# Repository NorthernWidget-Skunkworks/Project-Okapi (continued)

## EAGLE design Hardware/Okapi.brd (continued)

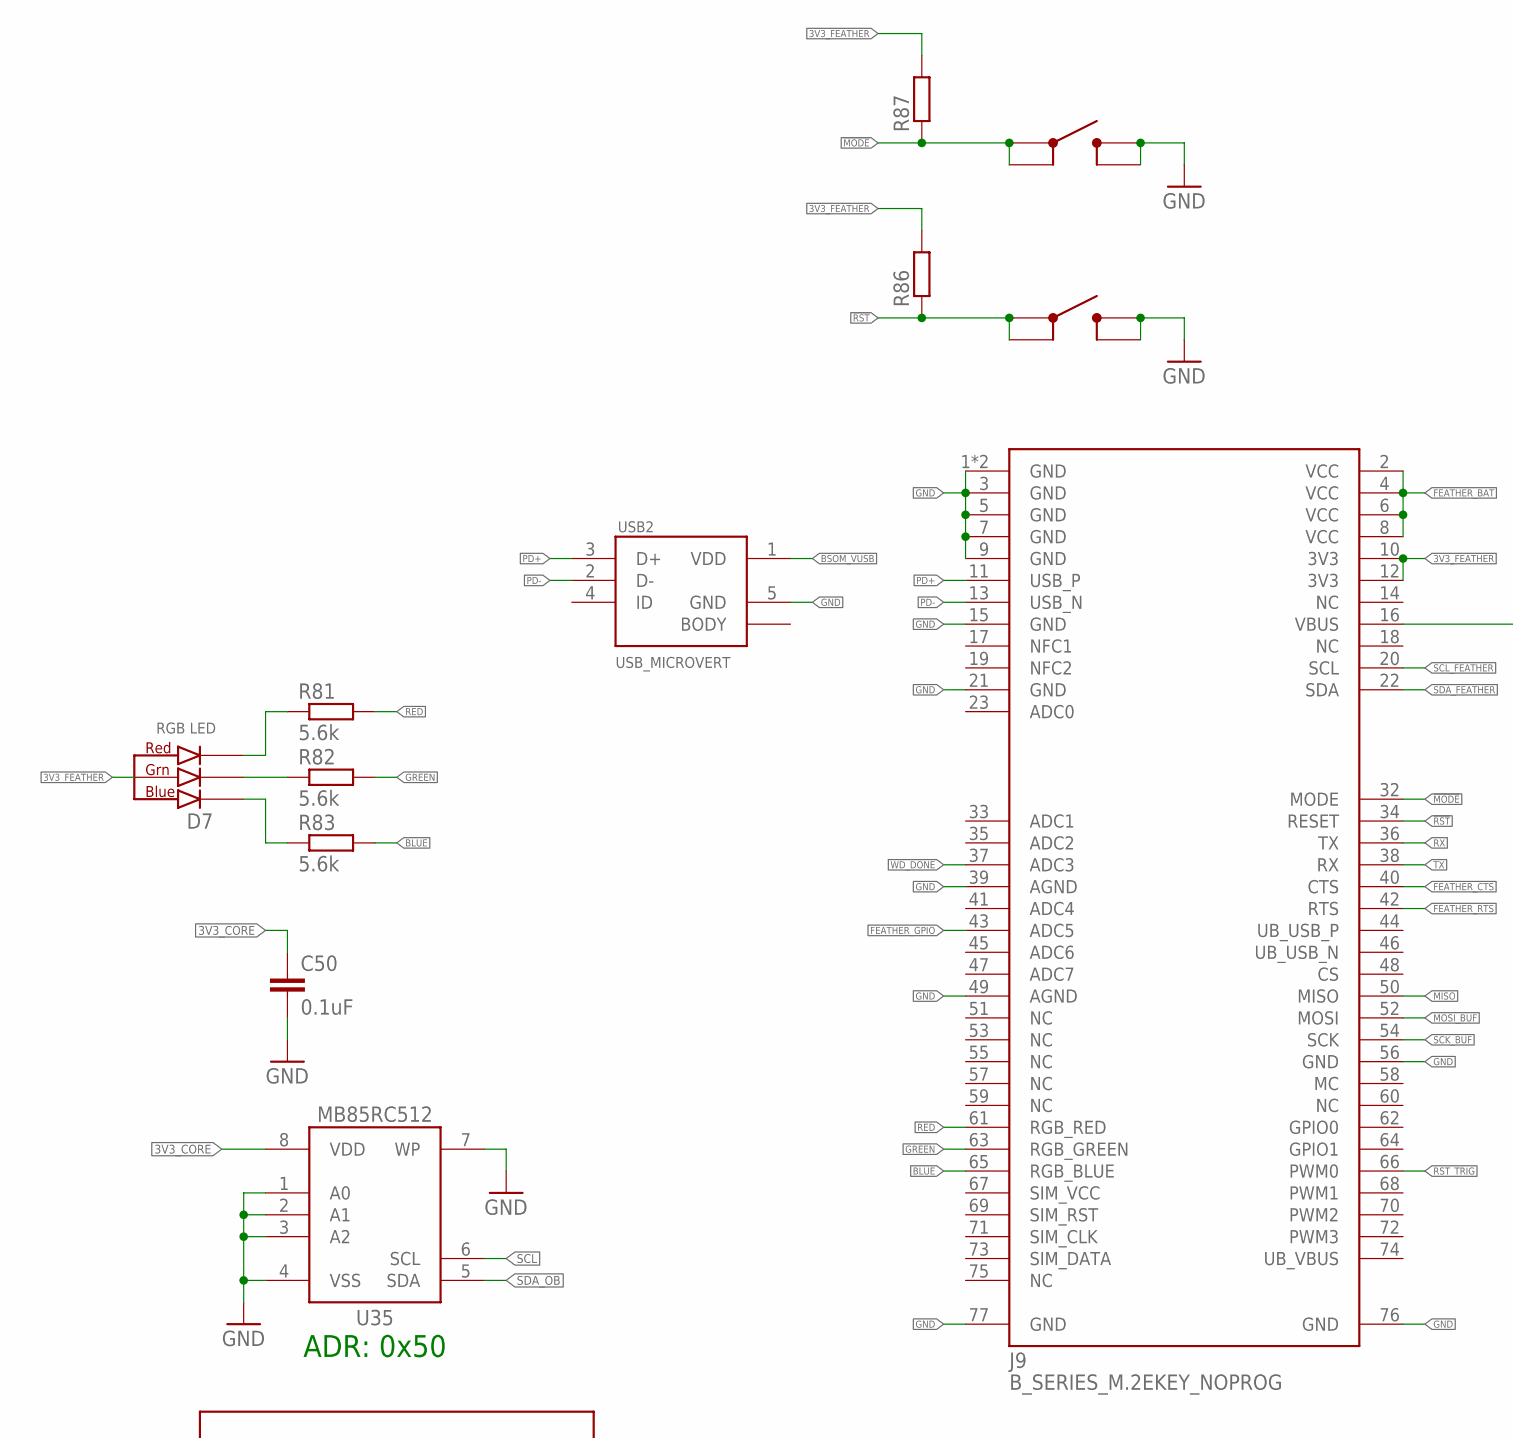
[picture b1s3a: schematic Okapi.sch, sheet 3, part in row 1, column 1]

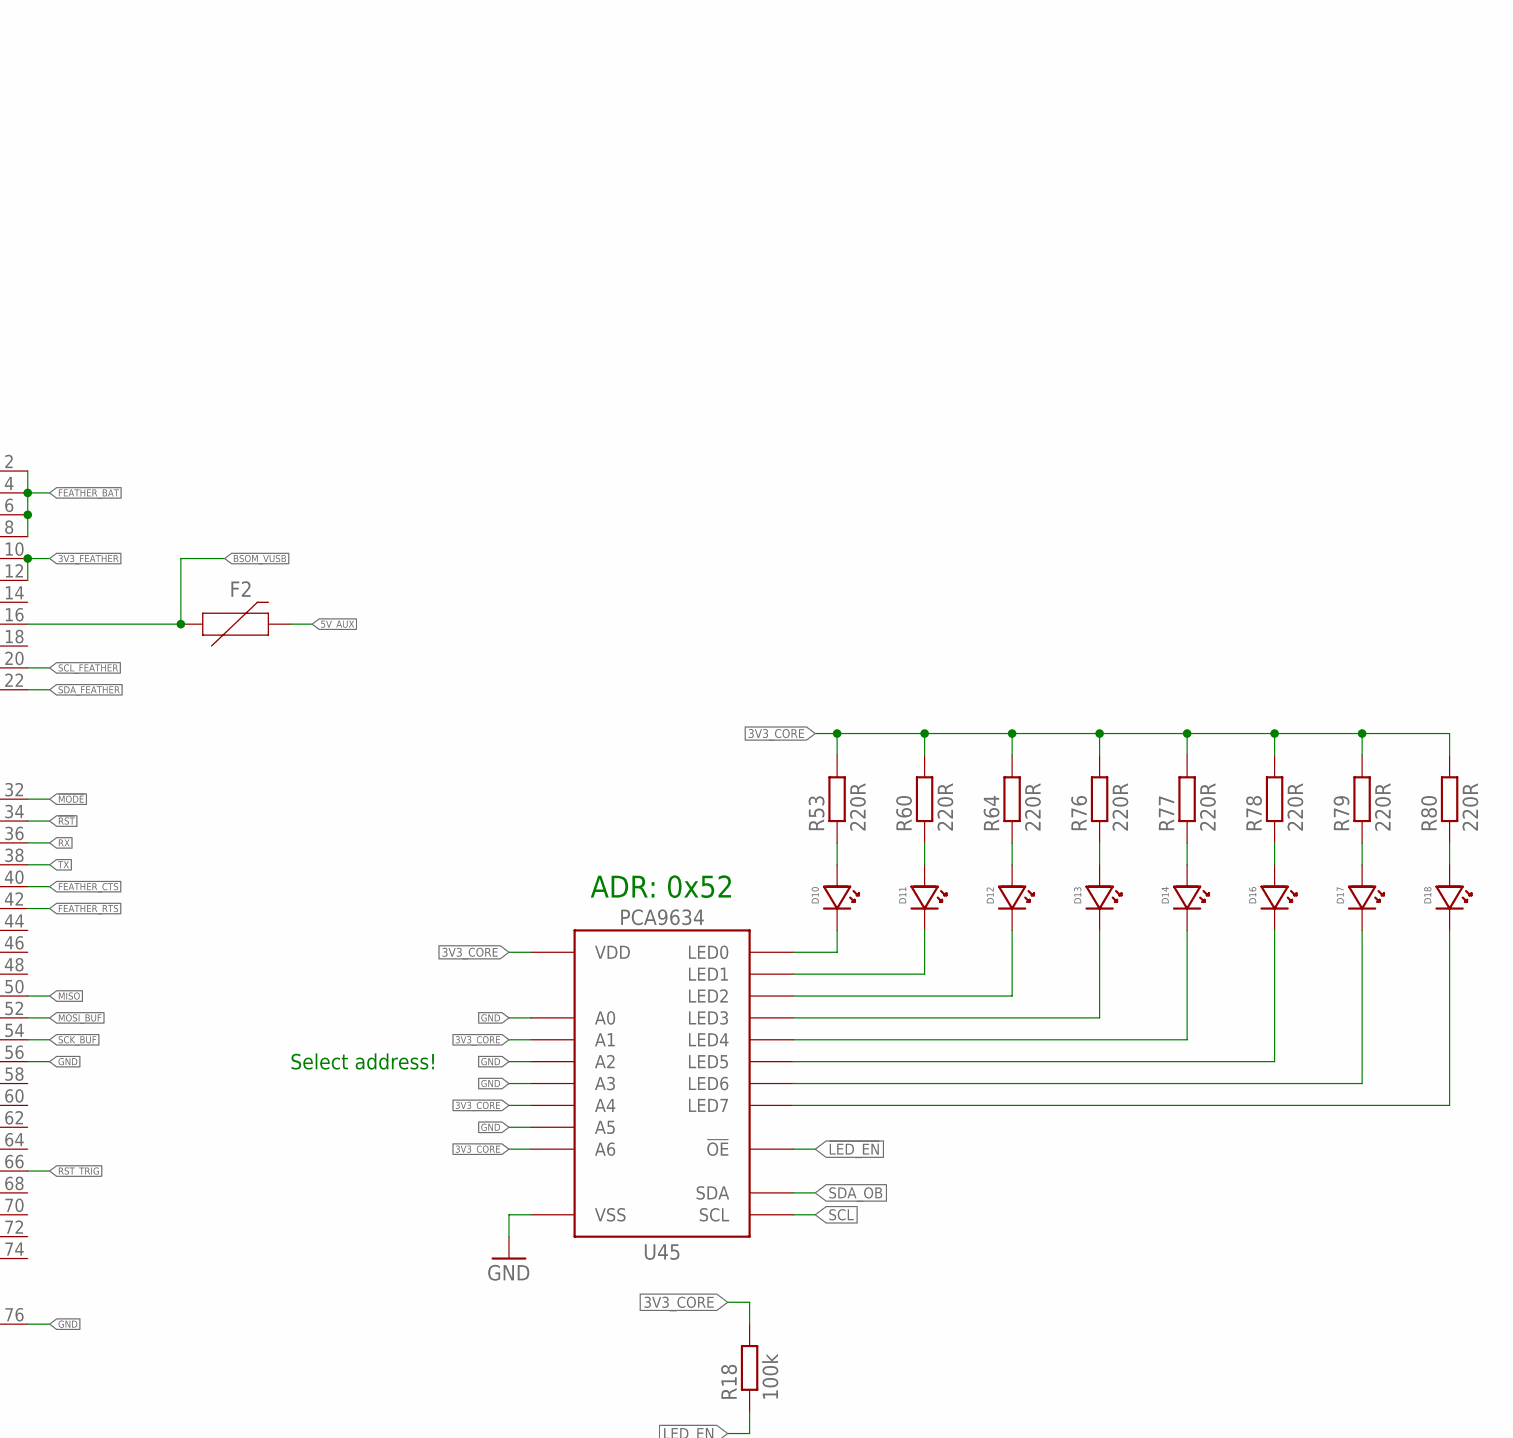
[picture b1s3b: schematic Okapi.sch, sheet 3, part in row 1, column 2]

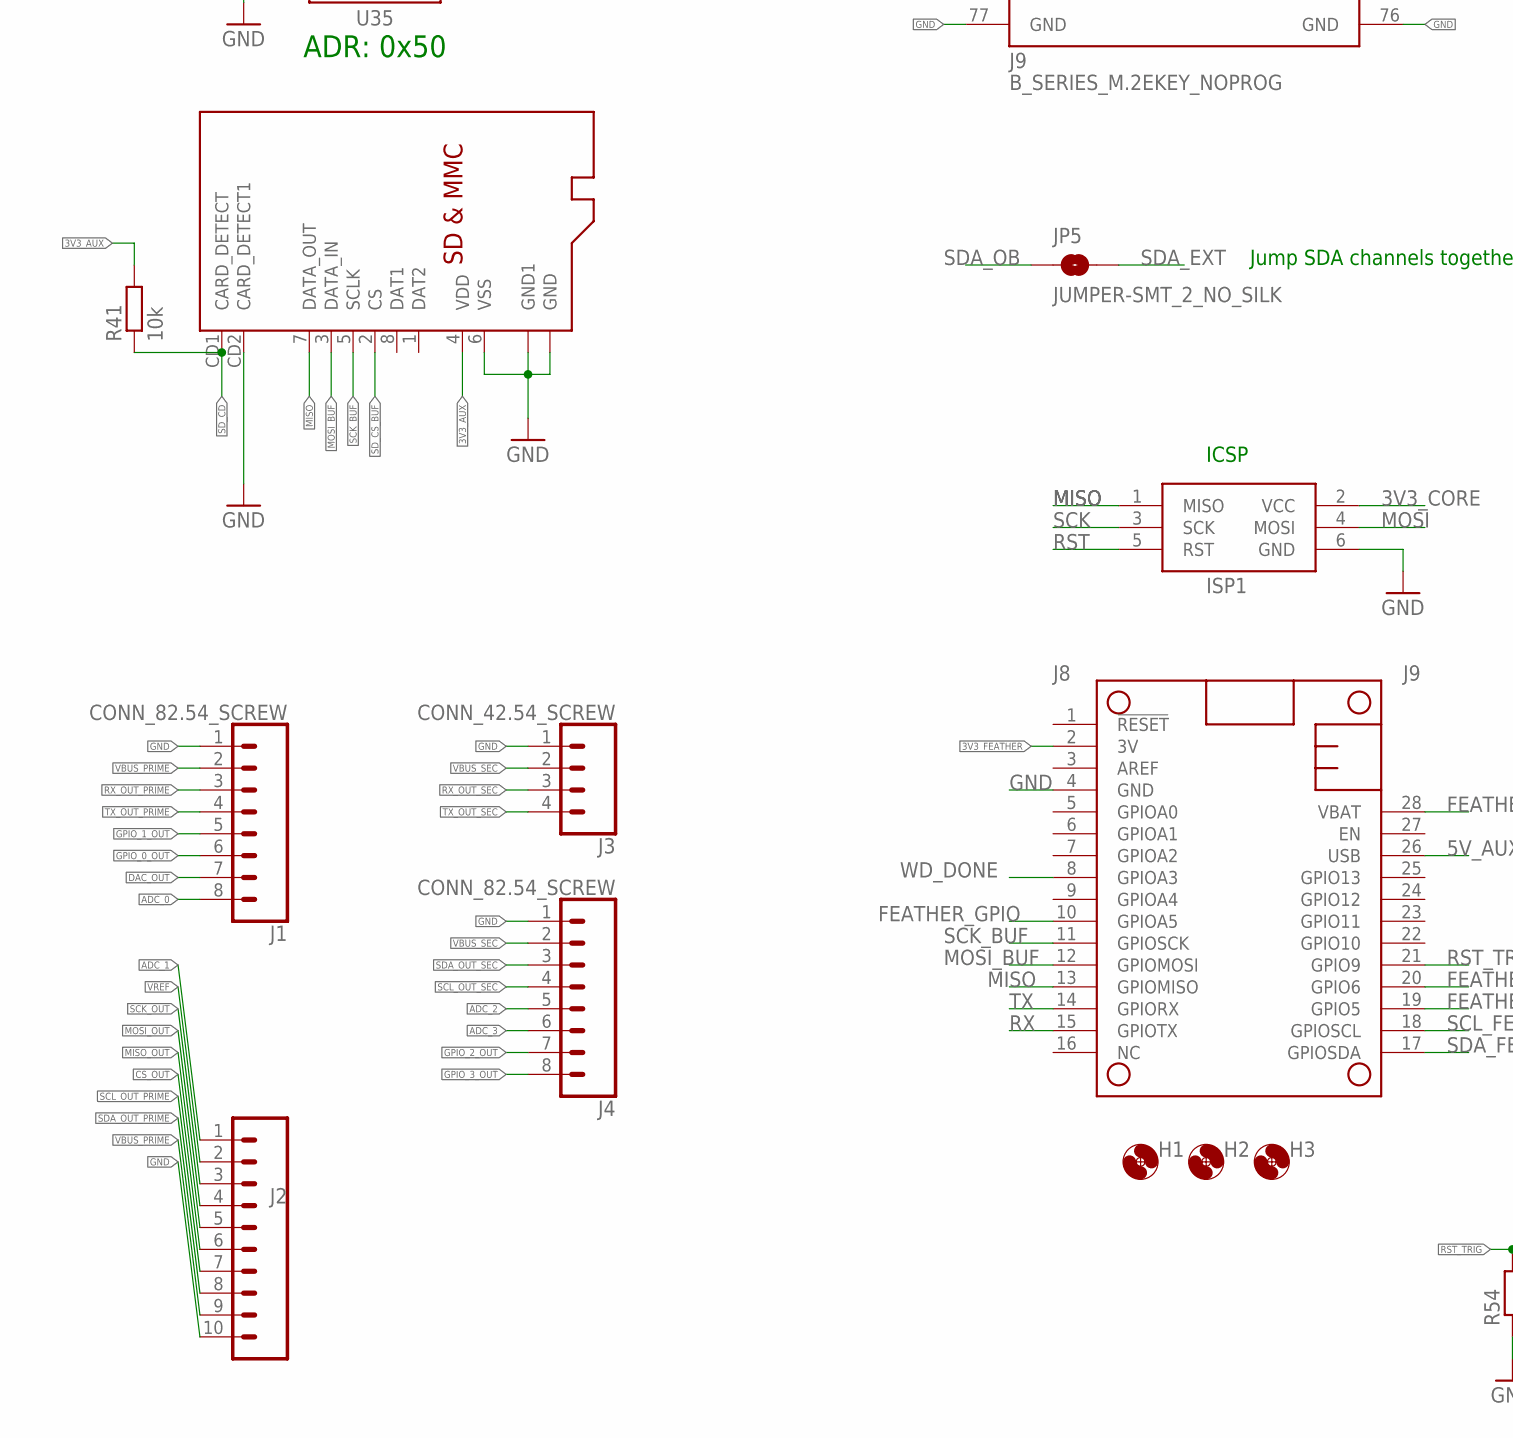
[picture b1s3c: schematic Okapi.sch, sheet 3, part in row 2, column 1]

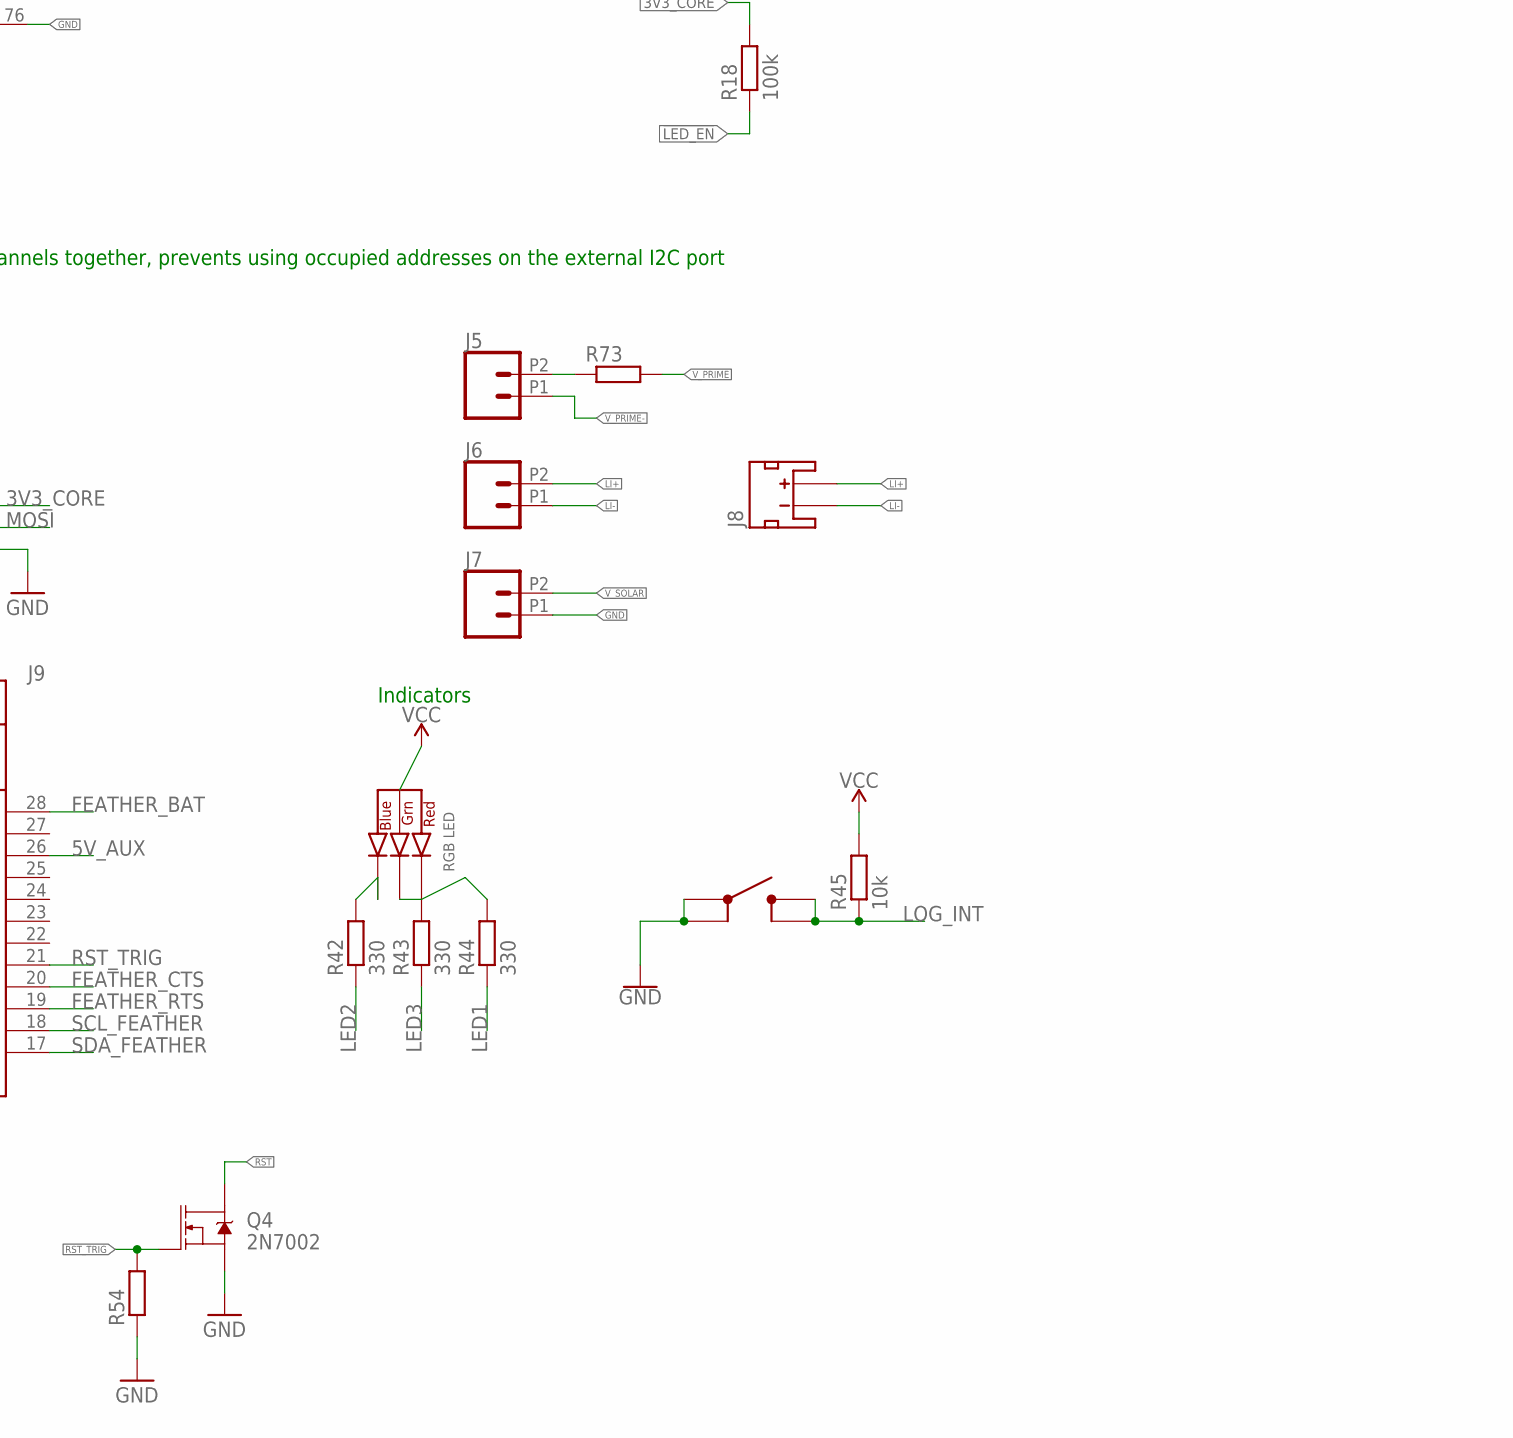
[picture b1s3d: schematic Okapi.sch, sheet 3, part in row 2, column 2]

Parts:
C50: 0.1uF; C0402
D5, D7: CLVBA-FKA
D10, D13, D16: LEDGREEN0603; LED_0603
D11, D14, D17: LEDYELLOW0603; LED_0603
D12, D18: LEDRED0603; LED_0603
F2: PPTC1.5A; 1206
H1, H2, H3: MOUNTING_HOLE4_NP; 4_40
ISP1: AVRISP-6; AVRISP; MPN 67997-206HLF; DIGIKEY 609-3234-ND
J1, J4: CONN_82.54_SCREW; 1X08_SCREW
J2: CONN_102.54_SCREW; 1X10_SCREW
J3: CONN_42.54_SCREW; 1X04_SCREW
J5, J6, J7: CONN_022.54_SCREW; 1X02_2.54_SCREWTERM
J8: JST_2MM_MALE; JST-2-SMD
J9: B_SERIES_M.2EKEY_NOPROG; PARTICLE_M.2EKEY_NOPROG
JP5: JUMPER-SMT_2_NO_SILK; SMT-JUMPER_2_NO_SILK
MS1: FEATHERWINGLAYOUT; FEATHERWING_MIN
Q4: 2N7002; SOT323
R18: 100k; R0402
R41: 10k; R0402
R42, R43, R44: 330; R0402; MPN RC0603FR-07330RL
R45: 10k; R0402; DIGIKEY 311-10.0KHRCT-ND
R53, R60, R64, R76, R77, R78, R79, R80: 220R; R0402
R54, R86, R87: R-EU_10KR0402; R0402
R73: R-EU_R0805; R0805
R81, R82, R83: 5.6k; R0402
S3, S6, S7: BUTTON4.2X3.2; SWITCH_4.2X3.2
SD1: MICROSDCD; MICROSD_CD
U35: MB85RC; SO08
U45: PCA9634QFN; QFN20_5X5
USB2: USB_MICROVERT; USB_MICRO_VERT_MOLEX

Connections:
3V3_AUX: R41.2, SD1.4 (VDD); also elsewhere on the board
3V3_CORE: C50.1, D5.2 (ANODE), ISP1.2 (VCC), R18.2, R45.2, R53.2, R60.2, R64.2, R76.2, R77.2, R78.2, R79.2, R80.2, U35.8 (VDD), U45.3 (A4), U45.15 (A6), U45.18 (VDD), U45.20 (A1); also elsewhere on the board
3V3_FEATHER: D7.2 (ANODE), J9.10 (3V3), J9.12 (3V3), MS1.2 (3V), R86.2, R87.2; also elsewhere on the board
5V_AUX: F2.2, MS1.26 (USB); also elsewhere on the board
!LED_EN: R18.1, U45.13 (!OE); also elsewhere on the board
!MODE: J9.32 (MODE), R87.1, S6.1, S6.2
!RST: J9.34 (RESET), R86.1, S7.1, S7.2
ADC_0: J1.8; also elsewhere on the board
ADC_1: J2.1; also elsewhere on the board
ADC_2: J4.5; also elsewhere on the board
ADC_3: J4.6; also elsewhere on the board
BLUE: J9.65 (RGB_BLUE), R83.2
BSOM_VUSB: F2.1, J9.16 (VBUS), USB2.1 (VDD)
CS_OUT: J2.6; also elsewhere on the board
DAC_OUT: J1.7; also elsewhere on the board
FEATHER_BAT: J9.2 (VCC), J9.4 (VCC), J9.6 (VCC), J9.8 (VCC), MS1.28 (VBAT); also elsewhere on the board
FEATHER_CTS: J9.40 (CTS), MS1.20 (GPIO6); also elsewhere on the board
FEATHER_GPIO: J9.43 (ADC5), MS1.10 (GPIOA5); also elsewhere on the board
FEATHER_RTS: J9.42 (RTS), MS1.19 (GPIO5); also elsewhere on the board
GND: C50.2, ISP1.6 (GND), J1.1, J2.10, J3.1, J4.1, J7.P1 (1), J9.1 (GND), J9.3 (GND), J9.5 (GND), J9.7 (GND), J9.9 (GND), J9.15 (GND), J9.21 (GND), J9.39 (AGND), J9.49 (AGND), J9.56 (GND), J9.76 (GND), J9.77 (GND), J9.GND, MS1.4 (GND), Q4.2 (S), R54.1, S3.1, S3.2, S6.3 (4), S6.4 (3), S7.3 (4), S7.4 (3), SD1.6 (VSS), SD1.CD2 (CARD_DETECT1), SD1.MT1 (GND), SD1.MT2 (GND1), SD1.MT3 (GND1), SD1.MT4 (GND1), U35.1 (A0), U35.2 (A1), U35.3 (A2), U35.4 (VSS), U35.7 (WP), U45.1 (A2), U45.2 (A3), U45.8 (VSS), U45.14 (A5), U45.19 (A0), U45.EP (VSS), USB2.5 (GND); also elsewhere on the board
GPIO_0_OUT: J1.6; also elsewhere on the board
GPIO_1_OUT: J1.5; also elsewhere on the board
GPIO_2_OUT: J4.7; also elsewhere on the board
GPIO_3_OUT: J4.8; also elsewhere on the board
GREEN: J9.63 (RGB_GREEN), R82.2
LED1: R44.1; also elsewhere on the board
LED2: R42.1; also elsewhere on the board
LED3: R43.1; also elsewhere on the board
LI+: J6.P2 (2), J8.2 (+); also elsewhere on the board
LI-: J6.P1 (1), J8.1 (-); also elsewhere on the board
LOG_INT: R45.1, S3.3 (4), S3.4 (3); also elsewhere on the board
MISO: ISP1.1 (MISO), J9.50 (MISO), MS1.13 (GPIOMISO), SD1.7 (DATA_OUT); also elsewhere on the board
MISO_OUT: J2.5; also elsewhere on the board
MOSI: ISP1.4 (MOSI); also elsewhere on the board
MOSI_BUF: J9.52 (MOSI), MS1.12 (GPIOMOSI), SD1.3 (DATA_IN); also elsewhere on the board
MOSI_OUT: J2.4; also elsewhere on the board
unnamed: D10.CATHODE, U45.4 (LED0)
unnamed: D5.3 (BLUE_CATH), R42.2
unnamed: D5.4 (GREEN_CATH), R43.2
unnamed: D5.1 (RED_CATH), R44.2
unnamed: D11.CATHODE, U45.5 (LED1)
unnamed: D12.CATHODE, U45.6 (LED2)
unnamed: D13.CATHODE, U45.7 (LED3)
unnamed: D14.CATHODE, U45.9 (LED4)
unnamed: D16.CATHODE, U45.10 (LED5)
unnamed: D17.CATHODE, U45.11 (LED6)
unnamed: D18.CATHODE, U45.12 (LED7)
unnamed: D10.ANODE, R53.1
unnamed: D11.ANODE, R60.1
unnamed: D12.ANODE, R64.1
unnamed: D13.ANODE, R76.1
unnamed: D14.ANODE, R77.1
unnamed: D16.ANODE, R78.1
unnamed: D17.ANODE, R79.1
unnamed: D18.ANODE, R80.1
unnamed: D7.1 (RED_CATH), R81.1
unnamed: D7.4 (GREEN_CATH), R82.1
unnamed: D7.3 (BLUE_CATH), R83.1
PD+: J9.11 (USB_P), USB2.3 (D+)
PD-: J9.13 (USB_N), USB2.2 (D-)
RED: J9.61 (RGB_RED), R81.2
RST: ISP1.5 (RST), Q4.3 (D); also elsewhere on the board
RST_TRIG: J9.66 (PWM0), MS1.21 (GPIO9), Q4.1 (G), R54.2
RX: J9.36 (TX), MS1.15 (GPIOTX); also elsewhere on the board
RX_OUT_PRIME: J1.3; also elsewhere on the board
RX_OUT_SEC: J3.3; also elsewhere on the board
SCK: ISP1.3 (SCK); also elsewhere on the board
SCK_BUF: J9.54 (SCK), MS1.11 (GPIOSCK), SD1.5 (SCLK); also elsewhere on the board
SCK_OUT: J2.3; also elsewhere on the board
SCL: U35.6 (SCL), U45.16 (SCL); also elsewhere on the board
SCL_FEATHER: J9.20 (SCL), MS1.18 (GPIOSCL); also elsewhere on the board
SCL_OUT_PRIME: J2.7; also elsewhere on the board
SCL_OUT_SEC: J4.4; also elsewhere on the board
SDA_EXT: JP5.2; also elsewhere on the board
SDA_FEATHER: J9.22 (SDA), MS1.17 (GPIOSDA); also elsewhere on the board
SDA_OB: JP5.1, U35.5 (SDA), U45.17 (SDA); also elsewhere on the board
SDA_OUT_PRIME: J2.8; also elsewhere on the board
SDA_OUT_SEC: J4.3; also elsewhere on the board
SD_CD: R41.1, SD1.CD1 (CARD_DETECT); also elsewhere on the board
SD_CS_BUF: SD1.2 (CS); also elsewhere on the board
SIM_VCC: J9.67 (SIM_VCC)
TX: J9.38 (RX), MS1.14 (GPIORX); also elsewhere on the board
TX_OUT_PRIME: J1.4; also elsewhere on the board
TX_OUT_SEC: J3.4; also elsewhere on the board
UB_VBUS: J9.74 (UB_VBUS)
VBUS_PRIME: J1.2, J2.9; also elsewhere on the board
VBUS_SEC: J3.2, J4.2; also elsewhere on the board
VREF: J2.2; also elsewhere on the board
V_PRIME: R73.2; also elsewhere on the board
V_PRIME-: J5.P1 (1); also elsewhere on the board
V_PRIME_SENSE: J5.P2 (2), R73.1; also elsewhere on the board
V_SOLAR: J7.P2 (2); also elsewhere on the board
WD_DONE: J9.37 (ADC3), MS1.8 (GPIOA3); also elsewhere on the board

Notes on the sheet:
Indicators
ICSP
Jump SDA channels together, prevents using occupied addresses on the external I2C port
ADR: 0x50
Select address!
ADR: 0x52

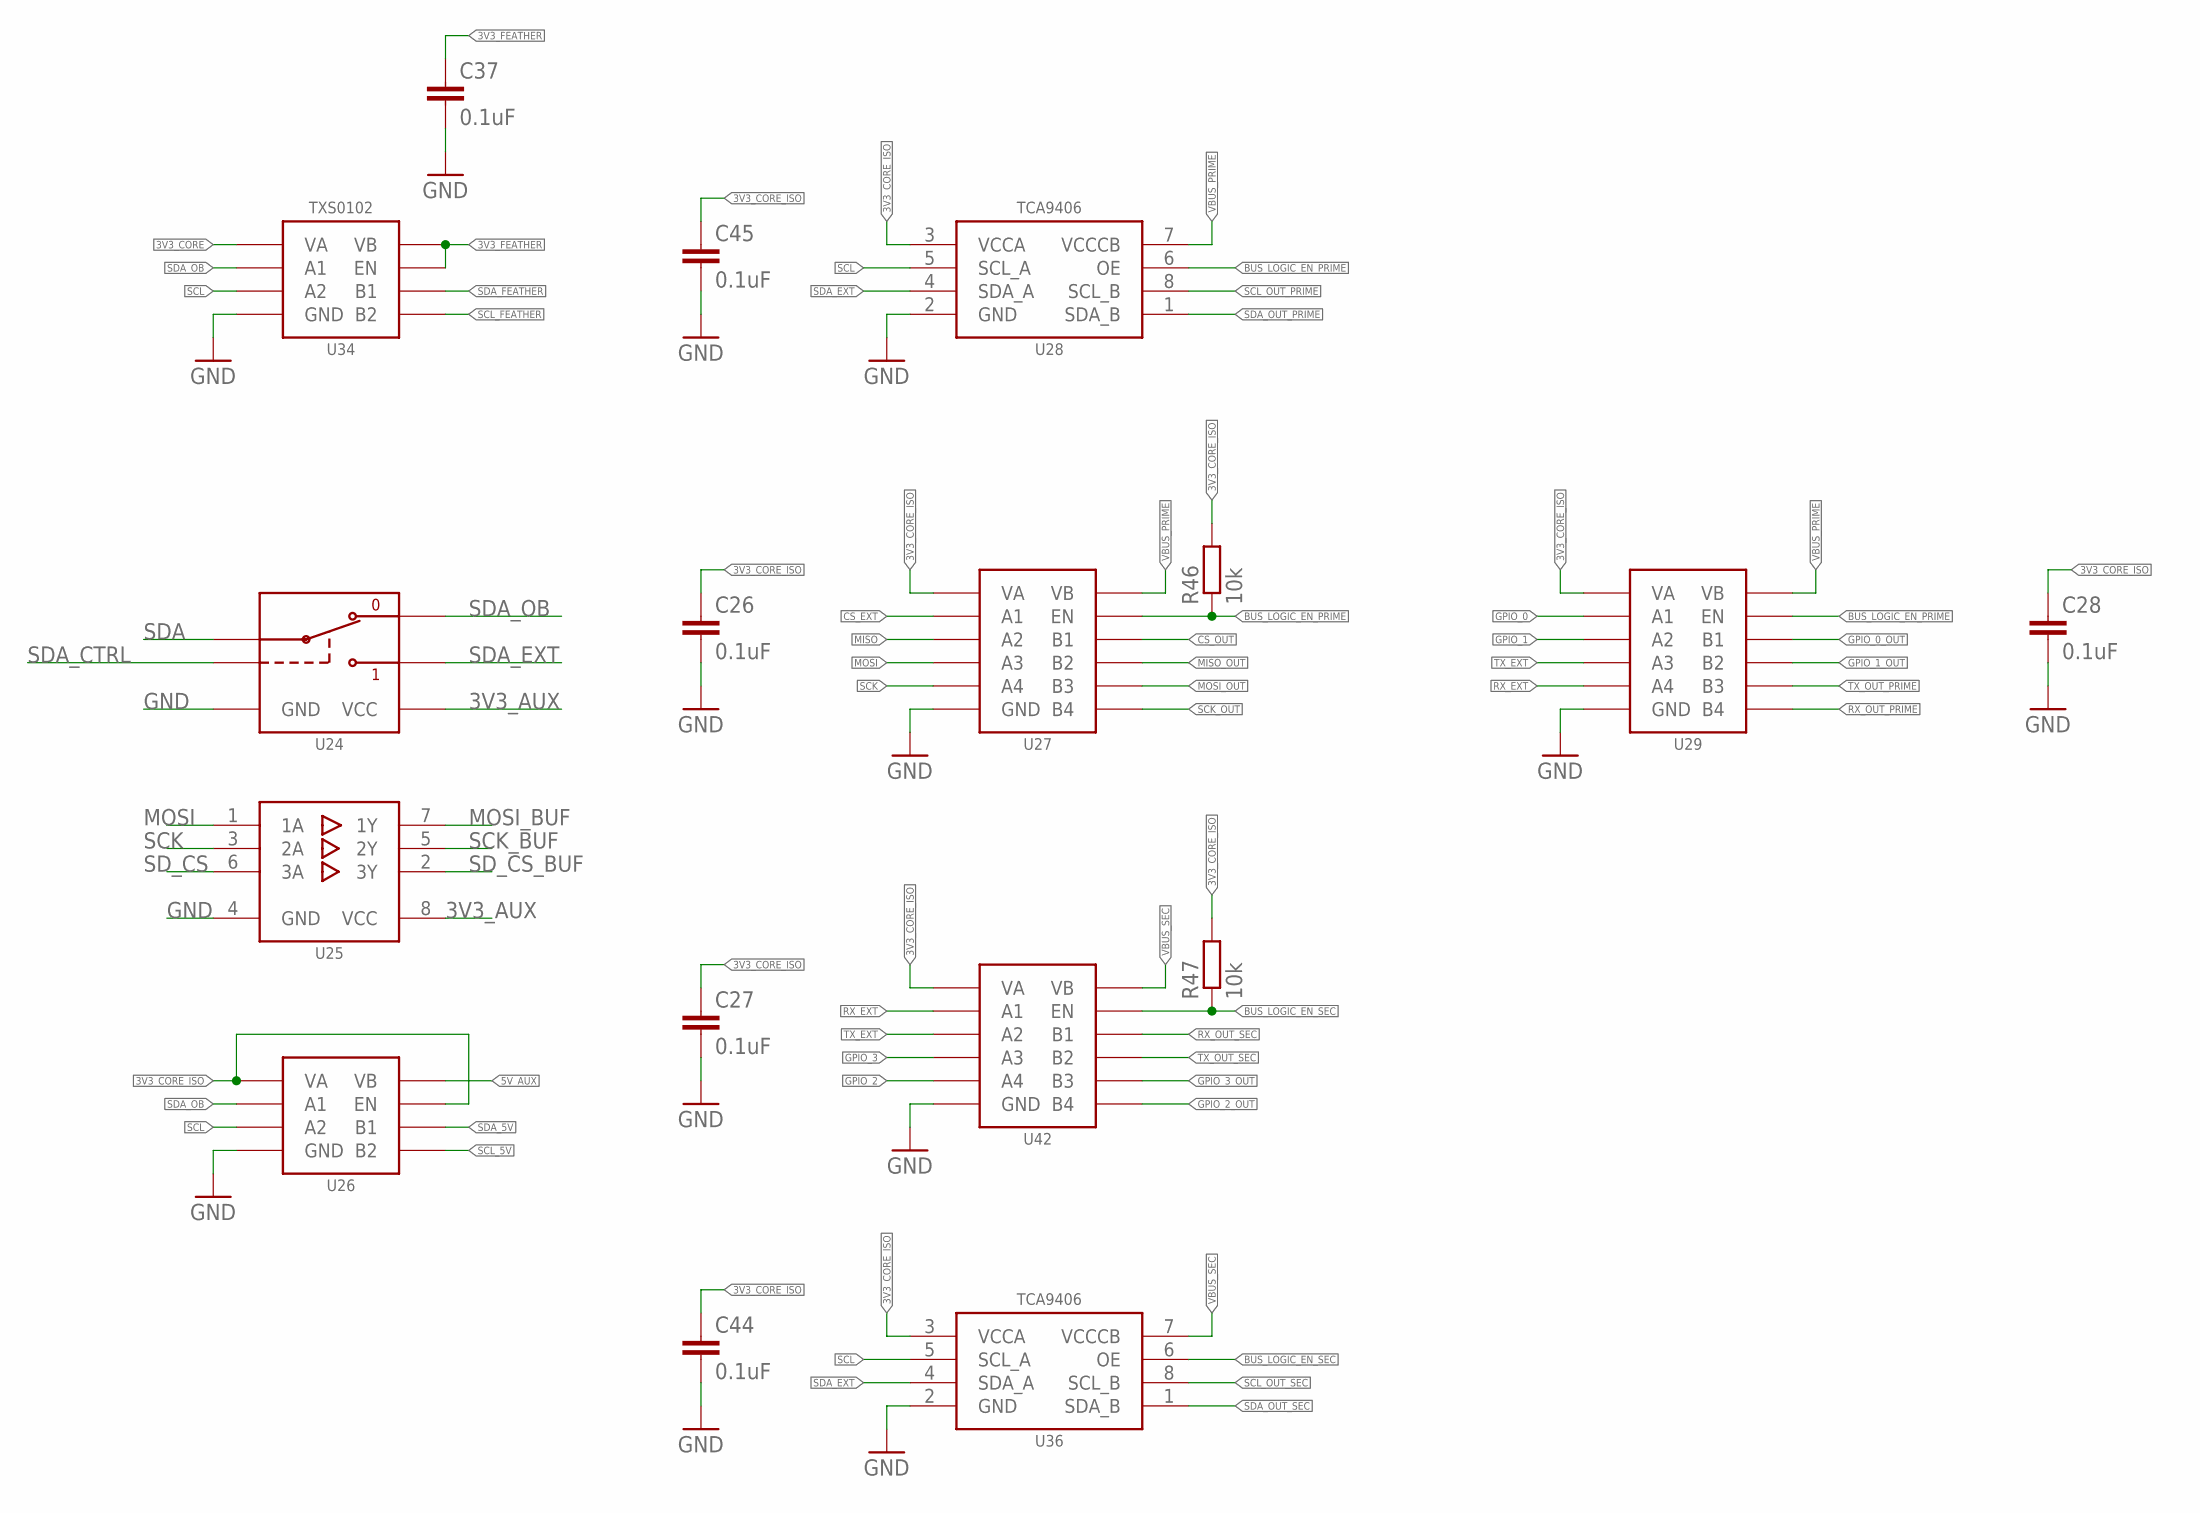
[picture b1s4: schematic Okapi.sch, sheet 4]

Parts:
C26, C27, C28, C37, C44, C45: 0.1uF; C0402
R46, R47: 10k; R0402
U24: SN74LVC1G3157DRL; DRL_R-PDSO-N6
U25: SN74AUP3G34DCU; DCU_(R-PDSO-G8)
U26, U34: TXS0102DQM; DQM_R-PX2SON-N8
U27, U29, U42: TXS0104RGY; RGY_S-PVQFN-N14
U28, U36: TCA9406DCU; DCU_(R-PDSO-G8)

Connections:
3V3_AUX: U24.5 (VCC), U25.8 (VCC); also elsewhere on the board
3V3_CORE: U34.1 (VA); also elsewhere on the board
3V3_CORE_ISO: C26.1, C27.1, C28.1, C44.1, C45.1, R46.2, R47.2, U26.1 (VA), U26.5 (EN), U27.1 (VA), U28.3 (VCCA), U29.1 (VA), U36.3 (VCCA), U42.1 (VA); also elsewhere on the board
3V3_FEATHER: C37.1, U34.5 (EN), U34.8 (VB); also elsewhere on the board
5V_AUX: U26.8 (VB); also elsewhere on the board
BUS_LOGIC_EN_PRIME: R46.1, U27.8 (EN), U28.6 (OE), U29.8 (EN); also elsewhere on the board
BUS_LOGIC_EN_SEC: R47.1, U36.6 (OE), U42.8 (EN); also elsewhere on the board
CS_EXT: U27.2 (A1); also elsewhere on the board
CS_OUT: U27.13 (B1); also elsewhere on the board
GND: C26.2, C27.2, C28.2, C37.2, C44.2, C45.2, U24.2 (GND), U25.4 (GND), U26.4 (GND), U27.7 (GND), U27.EP (GND), U28.2 (GND), U29.7 (GND), U29.EP (GND), U34.4 (GND), U36.2 (GND), U42.7 (GND), U42.EP (GND); also elsewhere on the board
GPIO_0: U29.2 (A1); also elsewhere on the board
GPIO_0_OUT: U29.13 (B1); also elsewhere on the board
GPIO_1: U29.3 (A2); also elsewhere on the board
GPIO_1_OUT: U29.12 (B2); also elsewhere on the board
GPIO_2: U42.5 (A4); also elsewhere on the board
GPIO_2_OUT: U42.10 (B4); also elsewhere on the board
GPIO_3: U42.4 (A3); also elsewhere on the board
GPIO_3_OUT: U42.11 (B3); also elsewhere on the board
MISO: U27.3 (A2); also elsewhere on the board
MISO_OUT: U27.12 (B2); also elsewhere on the board
MOSI: U25.1 (1A), U27.4 (A3); also elsewhere on the board
MOSI_BUF: U25.7 (1Y); also elsewhere on the board
MOSI_OUT: U27.11 (B3); also elsewhere on the board
RX_EXT: U29.5 (A4), U42.2 (A1); also elsewhere on the board
RX_OUT_PRIME: U29.10 (B4); also elsewhere on the board
RX_OUT_SEC: U42.13 (B1); also elsewhere on the board
SCK: U25.3 (2A), U27.5 (A4); also elsewhere on the board
SCK_BUF: U25.5 (2Y); also elsewhere on the board
SCK_OUT: U27.10 (B4); also elsewhere on the board
SCL: U26.3 (A2), U28.5 (SCL_A), U34.3 (A2), U36.5 (SCL_A); also elsewhere on the board
SCL_5V: U26.6 (B2); also elsewhere on the board
SCL_FEATHER: U34.6 (B2); also elsewhere on the board
SCL_OUT_PRIME: U28.8 (SCL_B); also elsewhere on the board
SCL_OUT_SEC: U36.8 (SCL_B); also elsewhere on the board
SDA: U24.4 (A); also elsewhere on the board
SDA_5V: U26.7 (B1); also elsewhere on the board
SDA_CTRL: U24.6 (S); also elsewhere on the board
SDA_EXT: U24.1 (B2), U28.4 (SDA_A), U36.4 (SDA_A); also elsewhere on the board
SDA_FEATHER: U34.7 (B1); also elsewhere on the board
SDA_OB: U24.3 (B1), U26.2 (A1), U34.2 (A1); also elsewhere on the board
SDA_OUT_PRIME: U28.1 (SDA_B); also elsewhere on the board
SDA_OUT_SEC: U36.1 (SDA_B); also elsewhere on the board
SD_CS: U25.6 (3A); also elsewhere on the board
SD_CS_BUF: U25.2 (3Y); also elsewhere on the board
TX_EXT: U29.4 (A3), U42.3 (A2); also elsewhere on the board
TX_OUT_PRIME: U29.11 (B3); also elsewhere on the board
TX_OUT_SEC: U42.12 (B2); also elsewhere on the board
VBUS_PRIME: U27.14 (VB), U28.7 (VCCCB), U29.14 (VB); also elsewhere on the board
VBUS_SEC: U36.7 (VCCCB), U42.14 (VB); also elsewhere on the board

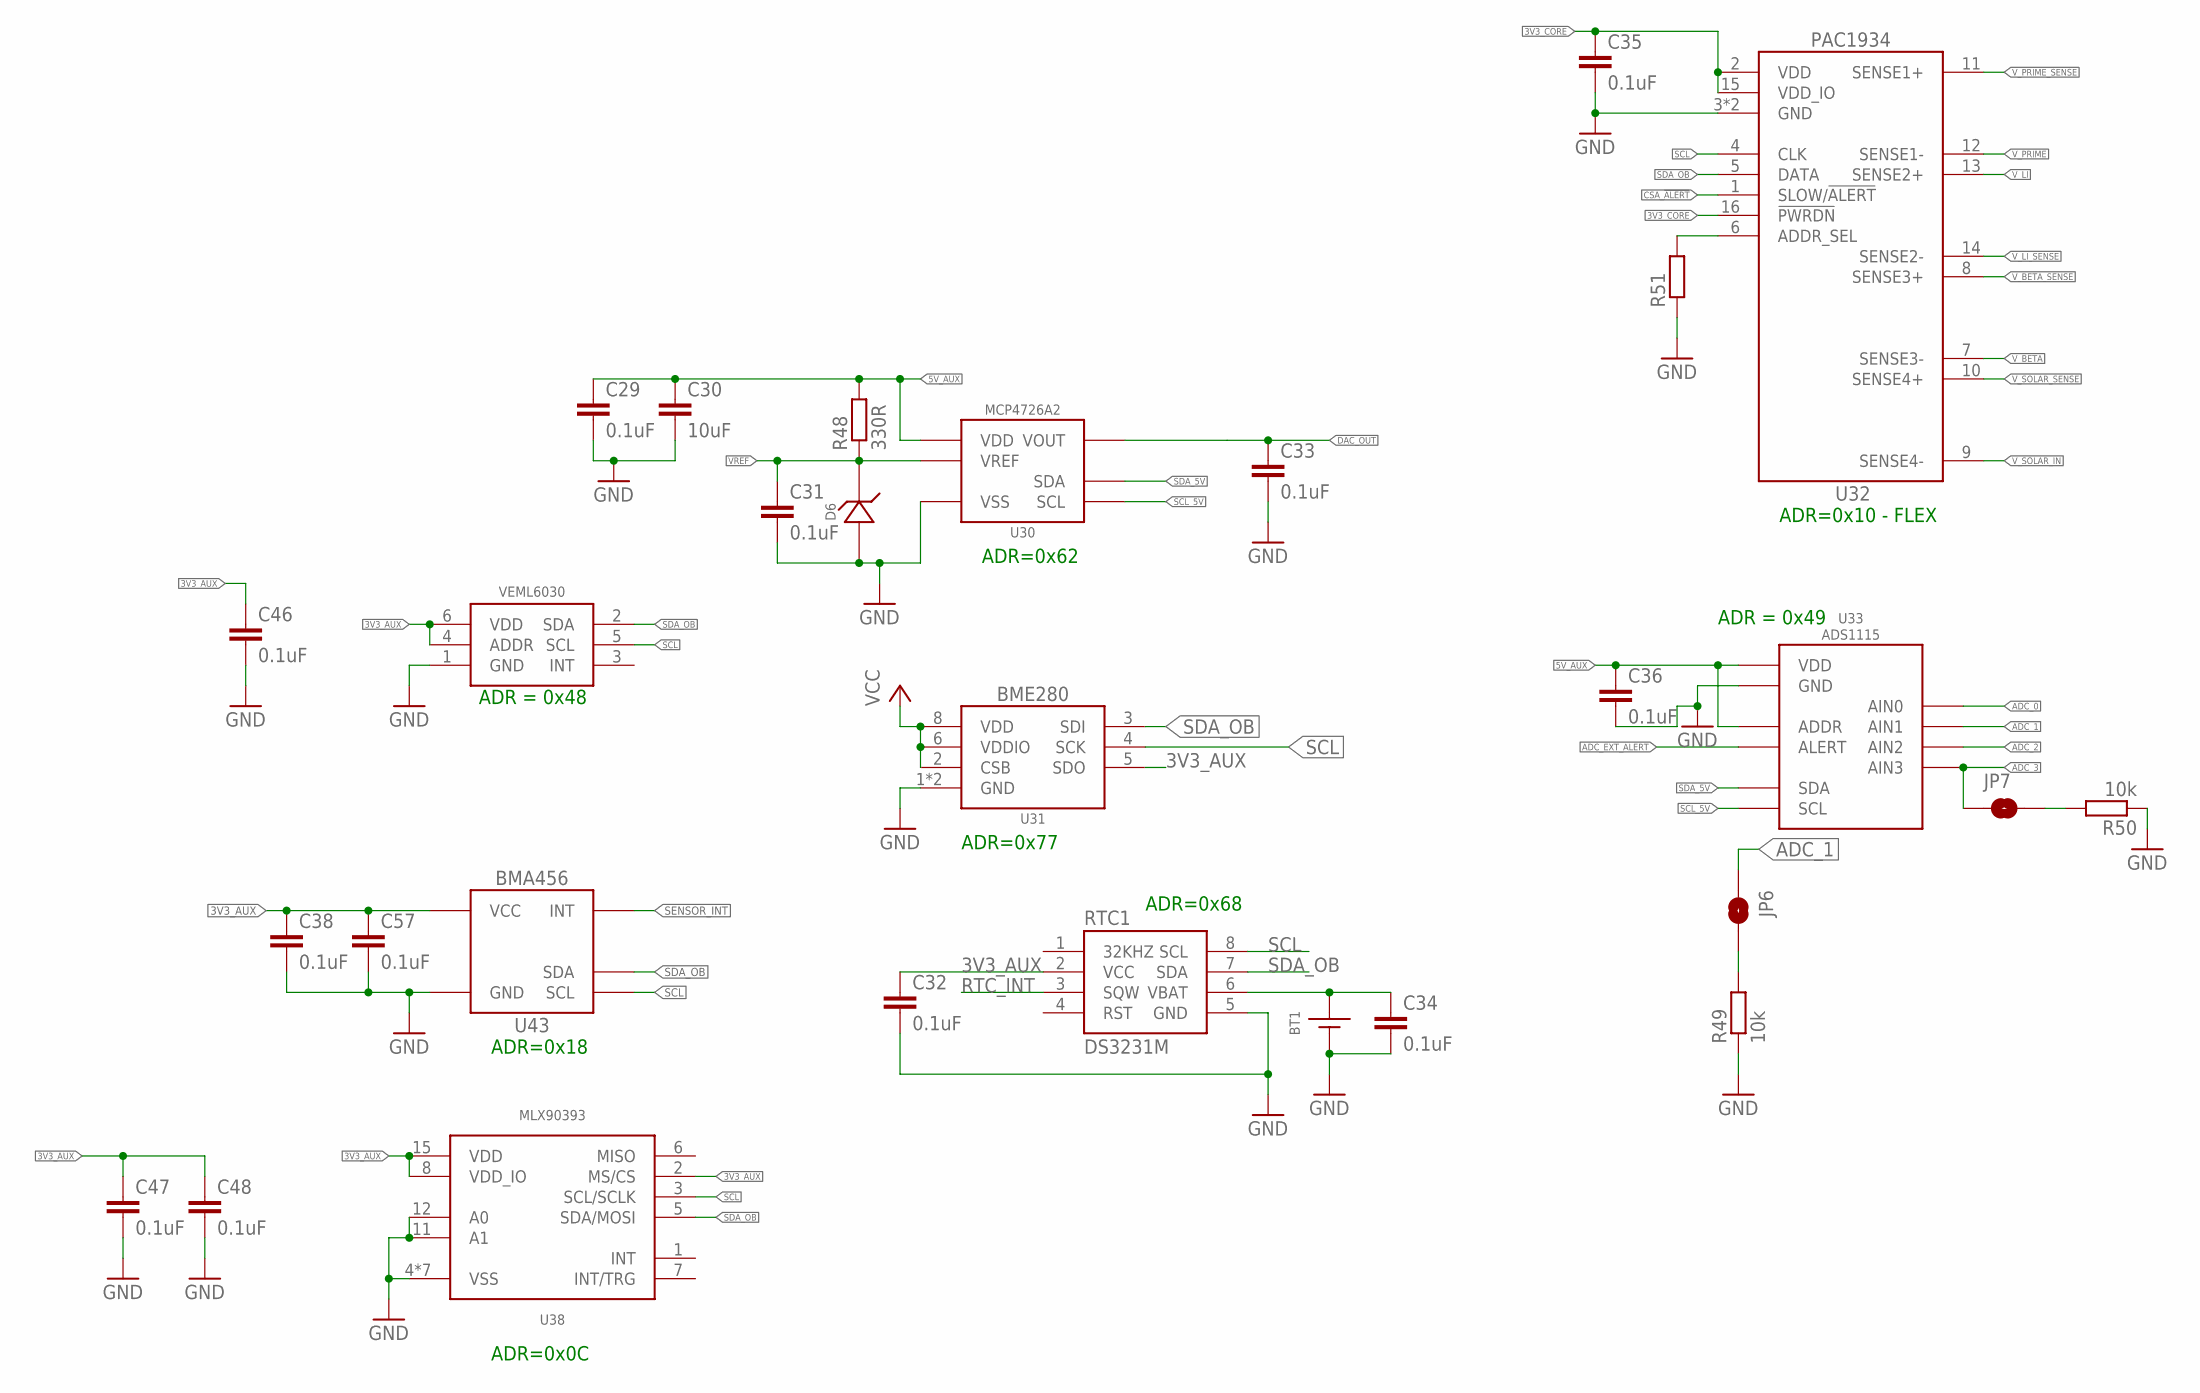
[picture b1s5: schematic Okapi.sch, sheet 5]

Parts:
BT1: BATTERY_COIN12MM; LINX_BAT-HLD-012-SMT
C29, C31, C32, C33, C34, C35, C36, C38, C46, C47, C48, C57: 0.1uF; C0402
C30: 10uF; C0805
D6: LM40402.5; SOT23-3
JP6, JP7: JUMPER-SMT_2_NO_SILK; SMT-JUMPER_2_NO_SILK
R48: 330R; R0603
R49, R50: 10k; R0603
R51: R-EU_R0402; R0402
RTC1: DS3231M; SO08
U30: MCP4726A2SOT-23; SOT23-6L
U31: BME280
U32: PAC1934QFN; QFN16
U33: ADS1115; VSSOP_10
U38: MLX90393; QFN16_3X3
U43: BMA456; LGA-12_2X2
U44: VEML6030

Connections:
3V3_AUX: C32.1, C38.1, C46.1, C47.1, C48.1, C57.1, RTC1.2 (VCC), U31.2 (CSB), U31.5 (SDO), U31.6 (VDDIO), U31.8 (VDD), U38.2 (MS/CS), U38.8 (VDD_IO), U38.15 (VDD), U43.3 (VCC), U43.7 (VCC), U43.10 (VCC), U44.4 (ADDR), U44.6 (VDD); also elsewhere on the board
3V3_CORE: C35.1, U32.2 (VDD), U32.15 (VDD_IO), U32.16 (!PWRDN); also elsewhere on the board
5V_AUX: C29.1, C30.1, C36.1, R48.2, U30.3 (VDD), U33.1 (ADDR), U33.8 (VDD); also elsewhere on the board
ADC_0: U33.4 (AIN0); also elsewhere on the board
ADC_1: JP6.1, U33.5 (AIN1); also elsewhere on the board
ADC_2: U33.6 (AIN2); also elsewhere on the board
ADC_3: JP7.1, U33.7 (AIN3); also elsewhere on the board
ADC_EXT_ALERT: U33.2 (ALERT); also elsewhere on the board
CSA_!ALERT: U32.1 (SLOW/!ALERT); also elsewhere on the board
DAC_OUT: C33.1, U30.1 (VOUT); also elsewhere on the board
GND: BT1.GND (-), C29.2, C30.2, C31.2, C32.2, C33.2, C34.2, C35.2, C36.2, C38.2, C46.2, C47.2, C48.2, C57.2, D6.2 (A), R49.1, R50.1, R51.1, RTC1.5 (GND), U30.2 (VSS), U31.1 (GND), U31.7 (GND), U32.3 (GND), U32.EP (GND), U33.3 (GND), U38.4 (VSS), U38.9 (VSS), U38.10 (VSS), U38.11 (A1), U38.12 (A0), U38.13 (VSS), U38.14 (VSS), U38.16 (VSS), U38.EP (VSS), U43.1 (GND), U43.8 (GND), U43.9 (GND), U44.1 (GND); also elsewhere on the board
unnamed: R51.2, U32.6 (ADDR_SEL)
unnamed: BT1.POWER0 (+), BT1.POWER1 (+), C34.1, RTC1.6 (VBAT)
unnamed: JP6.2, R49.2
unnamed: JP7.2, R50.2
RTC_INT: RTC1.3 (SQW); also elsewhere on the board
SCL: RTC1.8 (SCL), U31.4 (SCK), U32.4 (CLK), U38.3 (SCL/SCLK), U43.12 (SCL), U44.5 (SCL); also elsewhere on the board
SCL_5V: U30.5 (SCL), U33.10 (SCL); also elsewhere on the board
SDA_5V: U30.4 (SDA), U33.9 (SDA); also elsewhere on the board
SDA_OB: RTC1.7 (SDA), U31.3 (SDI), U32.5 (DATA), U38.5 (SDA/MOSI), U43.2 (SDA), U44.2 (SDA); also elsewhere on the board
SENSOR_INT: U43.5 (INT)
VREF: C31.1, D6.1 (C), R48.1, U30.6 (VREF); also elsewhere on the board
V_BETA: U32.7 (SENSE3-); also elsewhere on the board
V_BETA_SENSE: U32.8 (SENSE3+); also elsewhere on the board
V_LI: U32.13 (SENSE2+); also elsewhere on the board
V_LI_SENSE: U32.14 (SENSE2-); also elsewhere on the board
V_PRIME: U32.12 (SENSE1-); also elsewhere on the board
V_PRIME_SENSE: U32.11 (SENSE1+); also elsewhere on the board
V_SOLAR_IN: U32.9 (SENSE4-); also elsewhere on the board
V_SOLAR_SENSE: U32.10 (SENSE4+); also elsewhere on the board

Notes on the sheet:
ADR = 0x49
ADR = 0x48
ADR=0x77
ADR=0x18
ADR=0x68
ADR=0x10 - FLEX
ADR=0x62
ADR=0x0C
